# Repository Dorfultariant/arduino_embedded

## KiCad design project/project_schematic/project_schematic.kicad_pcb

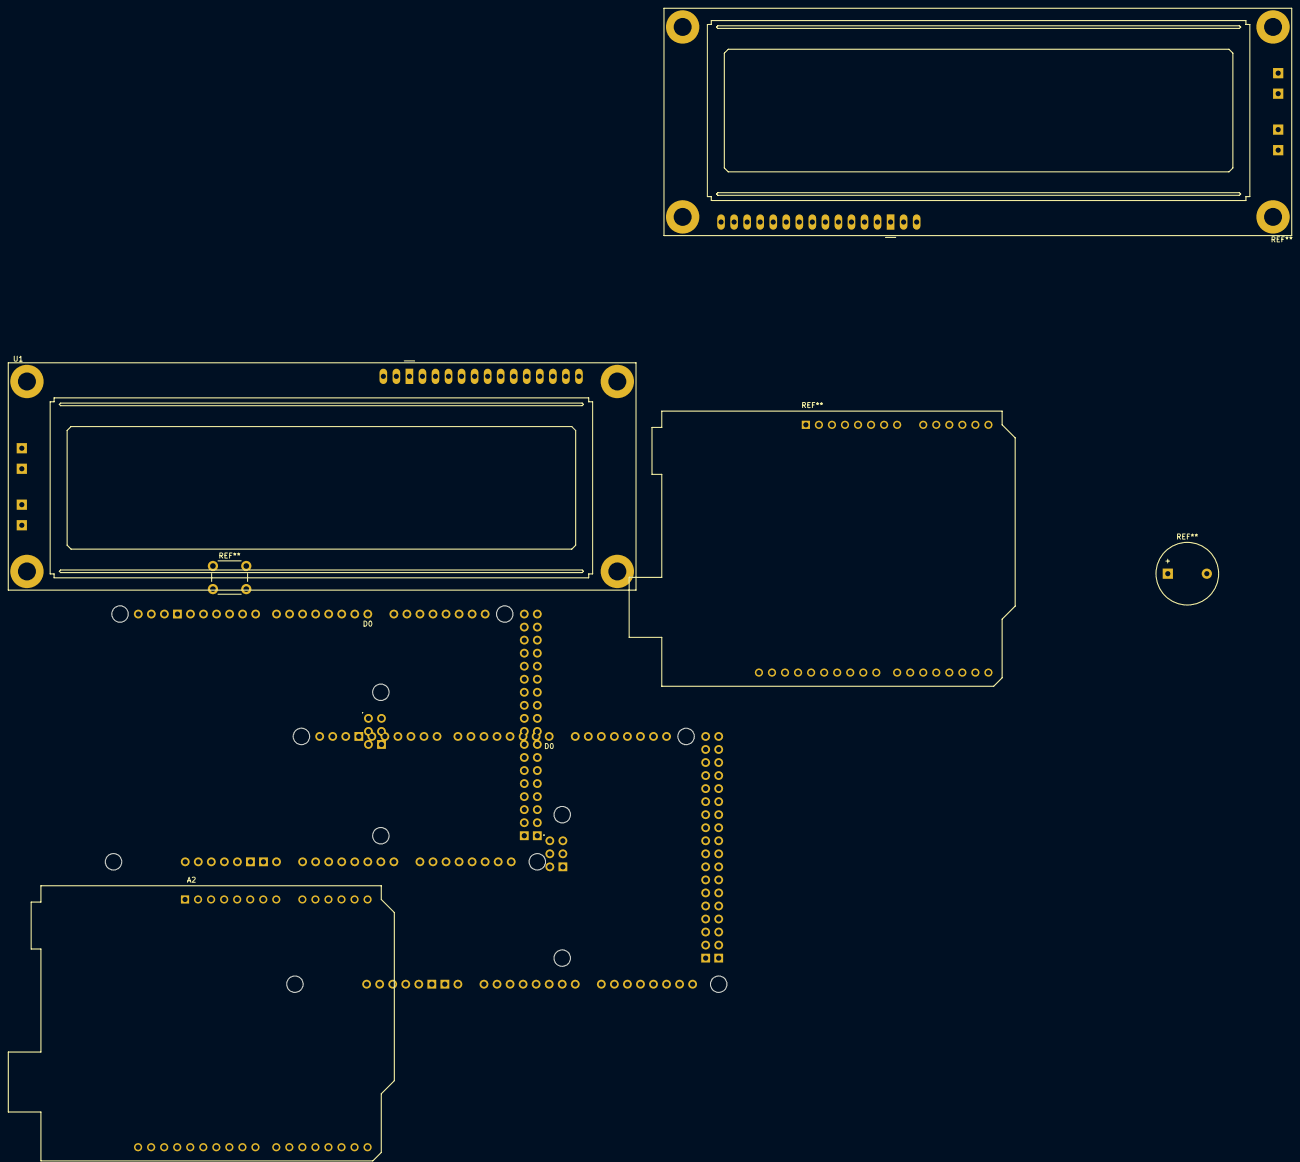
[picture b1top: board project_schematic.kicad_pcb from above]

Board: 2 copper layers, 4 parts (0 on the bottom side), 12 nets, no tracks yet.

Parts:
A1: Arduino_Mega2560_R3_Shield
A2: Arduino_UNO_R3
A**: Arduino_Mega2560_R3_Shield
U1: LCD-016N002L

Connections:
unnamed: A1.D20 (D20/SDA), A2.31 (SDA/A4)
unnamed: A1.D21 (D21/SCL), A2.32 (SCL/A5)
unnamed: A2.5 (+5V), U1.2 (VDD)
unnamed: A2.20 (D5), U1.14 (DB7)
unnamed: A2.21 (D6), U1.13 (DB6)
unnamed: A2.22 (D7), U1.12 (DB5)
unnamed: A2.23 (D8), U1.11 (DB4)
unnamed: A2.25 (D10), U1.4 (RS)
unnamed: A2.26 (D11), U1.5 (R/~W)
unnamed: A2.27 (D12), U1.6 (E)
unnamed: A1.GND6 (GND), A2.7 (GND)
unnamed: A2.6 (GND), U1.1 (VSS), U1.16 (K)

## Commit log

2024-04-26 Basic I2C structure
2024-04-27 EEPROM UART libs created for testing
2024-04-27 Initialization code
2024-04-27 Separate UART testbench created
2024-04-27 UART works so next test is i2c connection
2024-04-27 lib fix
2024-04-27 Keypad testing
2024-04-27 Added printf for testing
2024-04-27 Code verification
2024-04-27 Mods
2024-04-27 Keycode from user and verification
2024-04-29 Added a few things. Such as timer 1. and Timer 3.
2024-04-29 Changed code for tone function
2024-04-29 Updated mega pins
2024-04-29 Debug prints
2024-04-29 Mega testing
2024-04-29 Uno Testing
2024-04-29 Altered mega statemachine
2024-04-30 I2C data transfer conditioning
2024-04-30 Added I2C leds as output
2024-04-30 Data transfer testing
2024-05-02 Timer 0 testing on UNO. circuit schematic and clang-format added
2024-05-02 Indend width to 4
2024-05-02 oh notes
2024-05-02 added bad apple :)
2024-05-02 Uno code for data
2024-05-02 Moved note definitions to their own header file
2024-05-02 I2C additional testing
2024-05-02 KeyCode function edge case testing
2024-05-02 Edge case testing
2024-05-02 Checking of invalid chars
2024-05-03 waiting for data receive now in main loop and style fixes
2024-05-03 reading keys edge case testing
2024-05-03 Reading keys and checking for transmission success
2024-05-03 Oh right this is public repo
2024-05-03 More testing code because why not
2024-05-03 possible made main less bad
2024-05-03 actually added main function
2024-05-03 Small changes to transfer logic
2024-05-03 Compiles
2024-05-03 some documentation
2024-05-03 Ready for code review
2024-05-03 fixed it :D
2024-05-03 Went through the main.c codes of UNO and MEGA
2024-05-03 should work, needs to be tested
2024-05-03 removed CODE_ARRAY_LENGTH
2024-05-04 Small corrections and verified compilation otherwise LGTM
2024-05-04 Final commits
2024-05-04 Uno final commit
2024-05-04 Circuit schema update and video url
2024-05-04 Documentation
2024-05-05 Updated document
    Fixed by grammaly
2024-05-05 Last commit
